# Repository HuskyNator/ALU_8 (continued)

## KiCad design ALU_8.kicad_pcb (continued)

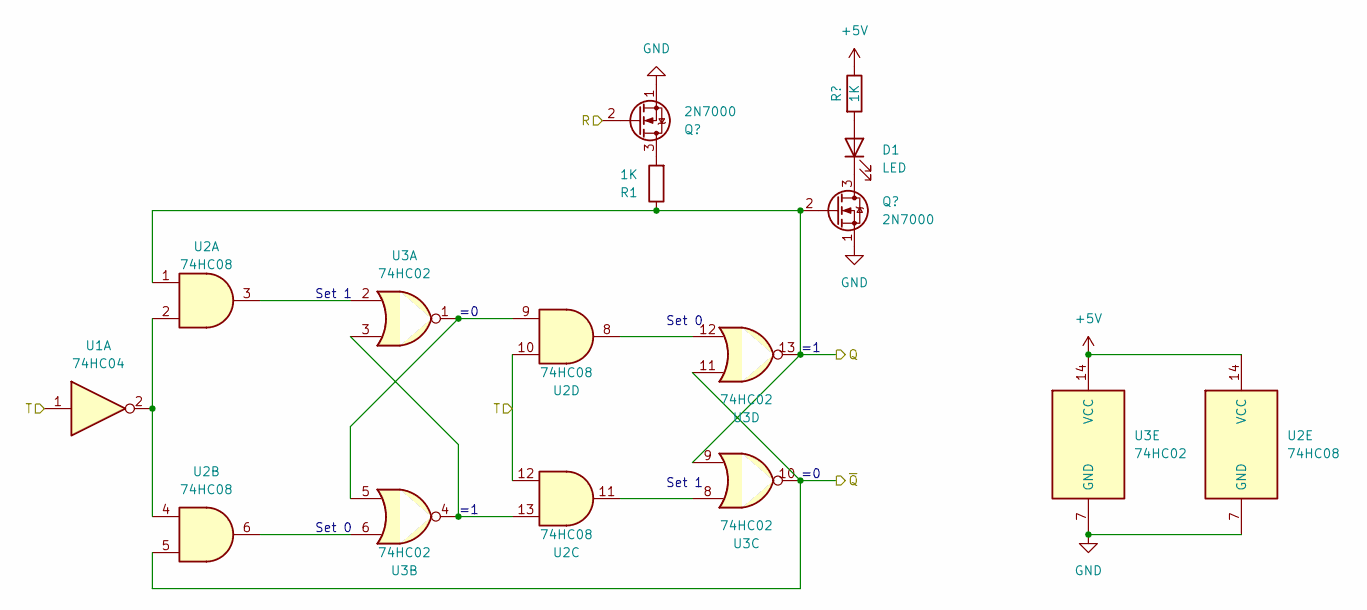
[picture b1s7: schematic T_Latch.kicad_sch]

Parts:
D1: LED; D_DO-34_SOD68_P2.54mm_Vertical_KathodeUp
Q1, Q2: 2N7000; TO-92_Inline
R1, R2: 1K; R_Axial_DIN0207_L6.3mm_D2.5mm_P7.62mm_Horizontal
U1: 74HC04; DIP-14_W7.62mm_Socket
U2: 74HC08; DIP-14_W7.62mm_Socket
U3: 74HC02; DIP-14_W7.62mm_Socket

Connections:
+5V: R2.1, U2.14 (VCC), U3.14 (VCC); also elsewhere on the board
/8 Toggle Latches/Toggle Latch/~Q: U2.5, U3.10, U3.11
/R: Q1.2 (G); also elsewhere on the board
/i0: Q2.2 (G), R1.1, U2.1, U3.9, U3.13; also elsewhere on the board
/s0: U1.1, U2.10, U2.12; also elsewhere on the board
/s1: U1.3; also elsewhere on the board
/s2: U1.5; also elsewhere on the board
/s3: U1.9; also elsewhere on the board
/s4: U1.11; also elsewhere on the board
/s5: U1.13; also elsewhere on the board
GND: Q1.1 (S), Q2.1 (S), U2.7 (GND), U3.7 (GND); also elsewhere on the board
unnamed: D1.2 (A), R2.2
unnamed: D1.1 (K), Q2.3 (D)
unnamed: Q1.3 (D), R1.2
unnamed: U1.2, U2.2, U2.4
unnamed 174: U1.4; also elsewhere on the board
unnamed 175: U1.6; also elsewhere on the board
unnamed 176: U1.8; also elsewhere on the board
unnamed 177: U1.10; also elsewhere on the board
unnamed 178: U1.12; also elsewhere on the board
unnamed: U2.3, U3.2
unnamed: U2.6, U3.6
unnamed: U2.8, U3.12
unnamed: U2.9, U3.1, U3.5
unnamed: U2.11, U3.8
unnamed: U2.13, U3.3, U3.4

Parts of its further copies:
D2, D3, D4, D5, D6, D7, D8: LED; D_DO-34_SOD68_P2.54mm_Vertical_KathodeUp
Q3, Q4, Q5, Q6, Q7, Q8, Q9, Q10, Q11, Q12, Q13, Q14, Q15, Q16: 2N7000; TO-92_Inline
R3, R4, R5, R6, R7, R8, R9, R10, R11, R12, R13, R14, R15, R16: 1K; R_Axial_DIN0207_L6.3mm_D2.5mm_P7.62mm_Horizontal
U4, U6, U8, U10, U12, U15, U17: 74HC08; DIP-14_W7.62mm_Socket
U5, U7, U9, U11, U13, U16, U18: 74HC02; DIP-14_W7.62mm_Socket

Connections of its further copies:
+5V: R4.1, R6.1, R8.1, R10.1, R12.1, R14.1, R16.1, U4.14 (VCC), U5.14 (VCC), U6.14 (VCC), U7.14 (VCC), U8.14 (VCC), U9.14 (VCC), U10.14 (VCC), U11.14 (VCC), U12.14 (VCC), U13.14 (VCC), U15.14 (VCC), U16.14 (VCC), U17.14 (VCC), U18.14 (VCC); also elsewhere on the board
/8 Toggle Latches/Toggle Latch1/~Q: U4.5, U5.10, U5.11
/8 Toggle Latches/Toggle Latch2/~Q: U6.5, U7.10, U7.11
/8 Toggle Latches/Toggle Latch3/~Q: U8.5, U9.10, U9.11
/8 Toggle Latches/Toggle Latch4/~Q: U10.5, U11.10, U11.11
/8 Toggle Latches/Toggle Latch5/~Q: U12.5, U13.10, U13.11
/8 Toggle Latches/Toggle Latch6/~Q: U15.5, U16.10, U16.11
/8 Toggle Latches/Toggle Latch7/~Q: U17.5, U18.10, U18.11
/R: Q3.2 (G), Q5.2 (G), Q7.2 (G), Q9.2 (G), Q11.2 (G), Q13.2 (G), Q15.2 (G); also elsewhere on the board
/i1: Q4.2 (G), R3.1, U4.1, U5.9, U5.13; also elsewhere on the board
/i2: Q6.2 (G), R5.1, U6.1, U7.9, U7.13; also elsewhere on the board
/i3: Q8.2 (G), R7.1, U8.1, U9.9, U9.13; also elsewhere on the board
/i4: Q10.2 (G), R9.1, U10.1, U11.9, U11.13; also elsewhere on the board
/i5: Q12.2 (G), R11.1, U12.1, U13.9, U13.13; also elsewhere on the board
/i6: Q14.2 (G), R13.1, U15.1, U16.9, U16.13; also elsewhere on the board
/i7: Q16.2 (G), R15.1, U17.1, U18.9, U18.13; also elsewhere on the board
/s1: U4.10, U4.12; also elsewhere on the board
/s2: U6.10, U6.12; also elsewhere on the board
/s3: U8.10, U8.12; also elsewhere on the board
/s4: U10.10, U10.12; also elsewhere on the board
/s5: U12.10, U12.12; also elsewhere on the board
/s6: U15.10, U15.12; also elsewhere on the board
/s7: U17.10, U17.12; also elsewhere on the board
GND: Q3.1 (S), Q4.1 (S), Q5.1 (S), Q6.1 (S), Q7.1 (S), Q8.1 (S), Q9.1 (S), Q10.1 (S), Q11.1 (S), Q12.1 (S), Q13.1 (S), Q14.1 (S), Q15.1 (S), Q16.1 (S), U4.7 (GND), U5.7 (GND), U6.7 (GND), U7.7 (GND), U8.7 (GND), U9.7 (GND), U10.7 (GND), U11.7 (GND), U12.7 (GND), U13.7 (GND), U15.7 (GND), U16.7 (GND), U17.7 (GND), U18.7 (GND); also elsewhere on the board
unnamed: D2.2 (A), R4.2
unnamed: D2.1 (K), Q4.3 (D)
unnamed: D3.2 (A), R6.2
unnamed: D3.1 (K), Q6.3 (D)
unnamed: D4.2 (A), R8.2
unnamed: D4.1 (K), Q8.3 (D)
unnamed: D5.2 (A), R10.2
unnamed: D5.1 (K), Q10.3 (D)
unnamed: D6.2 (A), R12.2
unnamed: D6.1 (K), Q12.3 (D)
unnamed: D7.2 (A), R14.2
unnamed: D7.1 (K), Q14.3 (D)
unnamed: D8.2 (A), R16.2
unnamed: D8.1 (K), Q16.3 (D)
unnamed: Q3.3 (D), R3.2
unnamed: Q5.3 (D), R5.2
unnamed: Q7.3 (D), R7.2
unnamed: Q9.3 (D), R9.2
unnamed: Q11.3 (D), R11.2
unnamed: Q13.3 (D), R13.2
unnamed: Q15.3 (D), R15.2
unnamed 174: U4.2, U4.4; also elsewhere on the board
unnamed 175: U6.2, U6.4; also elsewhere on the board
unnamed 176: U8.2, U8.4; also elsewhere on the board
unnamed 177: U10.2, U10.4; also elsewhere on the board
unnamed 178: U12.2, U12.4; also elsewhere on the board
unnamed: U4.3, U5.2
unnamed: U4.6, U5.6
unnamed: U4.8, U5.12
unnamed: U4.9, U5.1, U5.5
unnamed: U4.11, U5.8
unnamed: U4.13, U5.3, U5.4
unnamed: U6.3, U7.2
unnamed: U6.6, U7.6
unnamed: U6.8, U7.12
unnamed: U6.9, U7.1, U7.5
unnamed: U6.11, U7.8
unnamed: U6.13, U7.3, U7.4
unnamed: U8.3, U9.2
unnamed: U8.6, U9.6
unnamed: U8.8, U9.12
unnamed: U8.9, U9.1, U9.5
unnamed: U8.11, U9.8
unnamed: U8.13, U9.3, U9.4
unnamed: U10.3, U11.2
unnamed: U10.6, U11.6
unnamed: U10.8, U11.12
unnamed: U10.9, U11.1, U11.5
unnamed: U10.11, U11.8
unnamed: U10.13, U11.3, U11.4
unnamed: U12.3, U13.2
unnamed: U12.6, U13.6
unnamed: U12.8, U13.12
unnamed: U12.9, U13.1, U13.5
unnamed: U12.11, U13.8
unnamed: U12.13, U13.3, U13.4
unnamed 215: U15.2, U15.4; also elsewhere on the board
unnamed 216: U17.2, U17.4; also elsewhere on the board
unnamed: U15.3, U16.2
unnamed: U15.6, U16.6
unnamed: U15.8, U16.12
unnamed: U15.9, U16.1, U16.5
unnamed: U15.11, U16.8
unnamed: U15.13, U16.3, U16.4
unnamed: U17.3, U18.2
unnamed: U17.6, U18.6
unnamed: U17.8, U18.12
unnamed: U17.9, U18.1, U18.5
unnamed: U17.11, U18.8
unnamed: U17.13, U18.3, U18.4

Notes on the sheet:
Set 0
Set 1

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
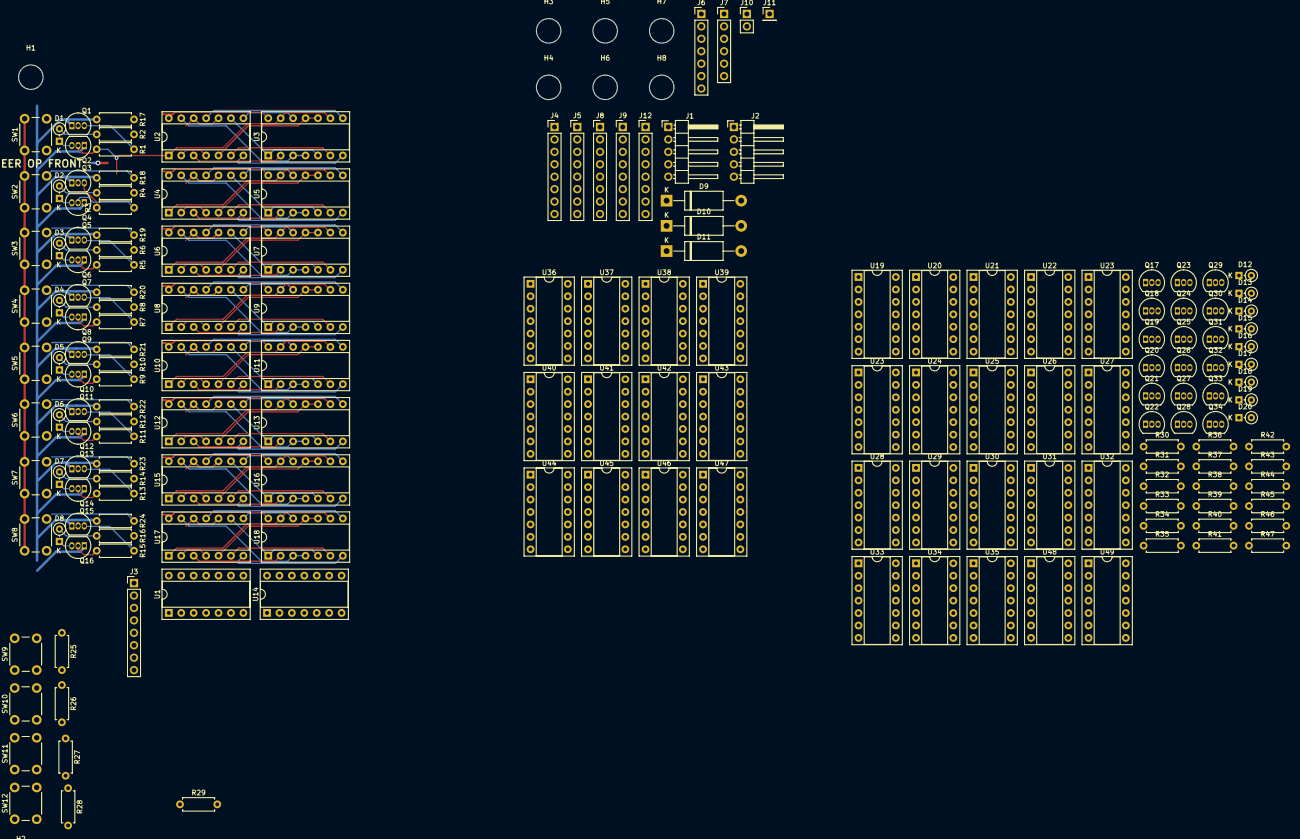
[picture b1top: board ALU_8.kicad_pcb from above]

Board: 2 copper layers, 183 parts (0 on the bottom side), 295 nets.

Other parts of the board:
U23#2: 74HC08; DIP-14_W7.62mm_Socket

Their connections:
+5V: U23#2.14 (VCC); also elsewhere on the board
/D4: U23#2.1; also elsewhere on the board
/E: U23#2.2, U23#2.4; also elsewhere on the board
/Memory/~E: U23#2.9, U23#2.13; also elsewhere on the board
GND: U23#2.7 (GND); also elsewhere on the board
unnamed 167: U23#2.10; also elsewhere on the board
unnamed 219: U23#2.5; also elsewhere on the board
unnamed 243: U23#2.3; also elsewhere on the board
unnamed 244: U23#2.6; also elsewhere on the board
unnamed 245: U23#2.8; also elsewhere on the board
unnamed 246: U23#2.11; also elsewhere on the board
unnamed 247: U23#2.12; also elsewhere on the board

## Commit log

2024-01-09 Initialize to current project files
2024-01-09 Write Readme & add backup ignore
2024-01-10 Test Markdown Embed
